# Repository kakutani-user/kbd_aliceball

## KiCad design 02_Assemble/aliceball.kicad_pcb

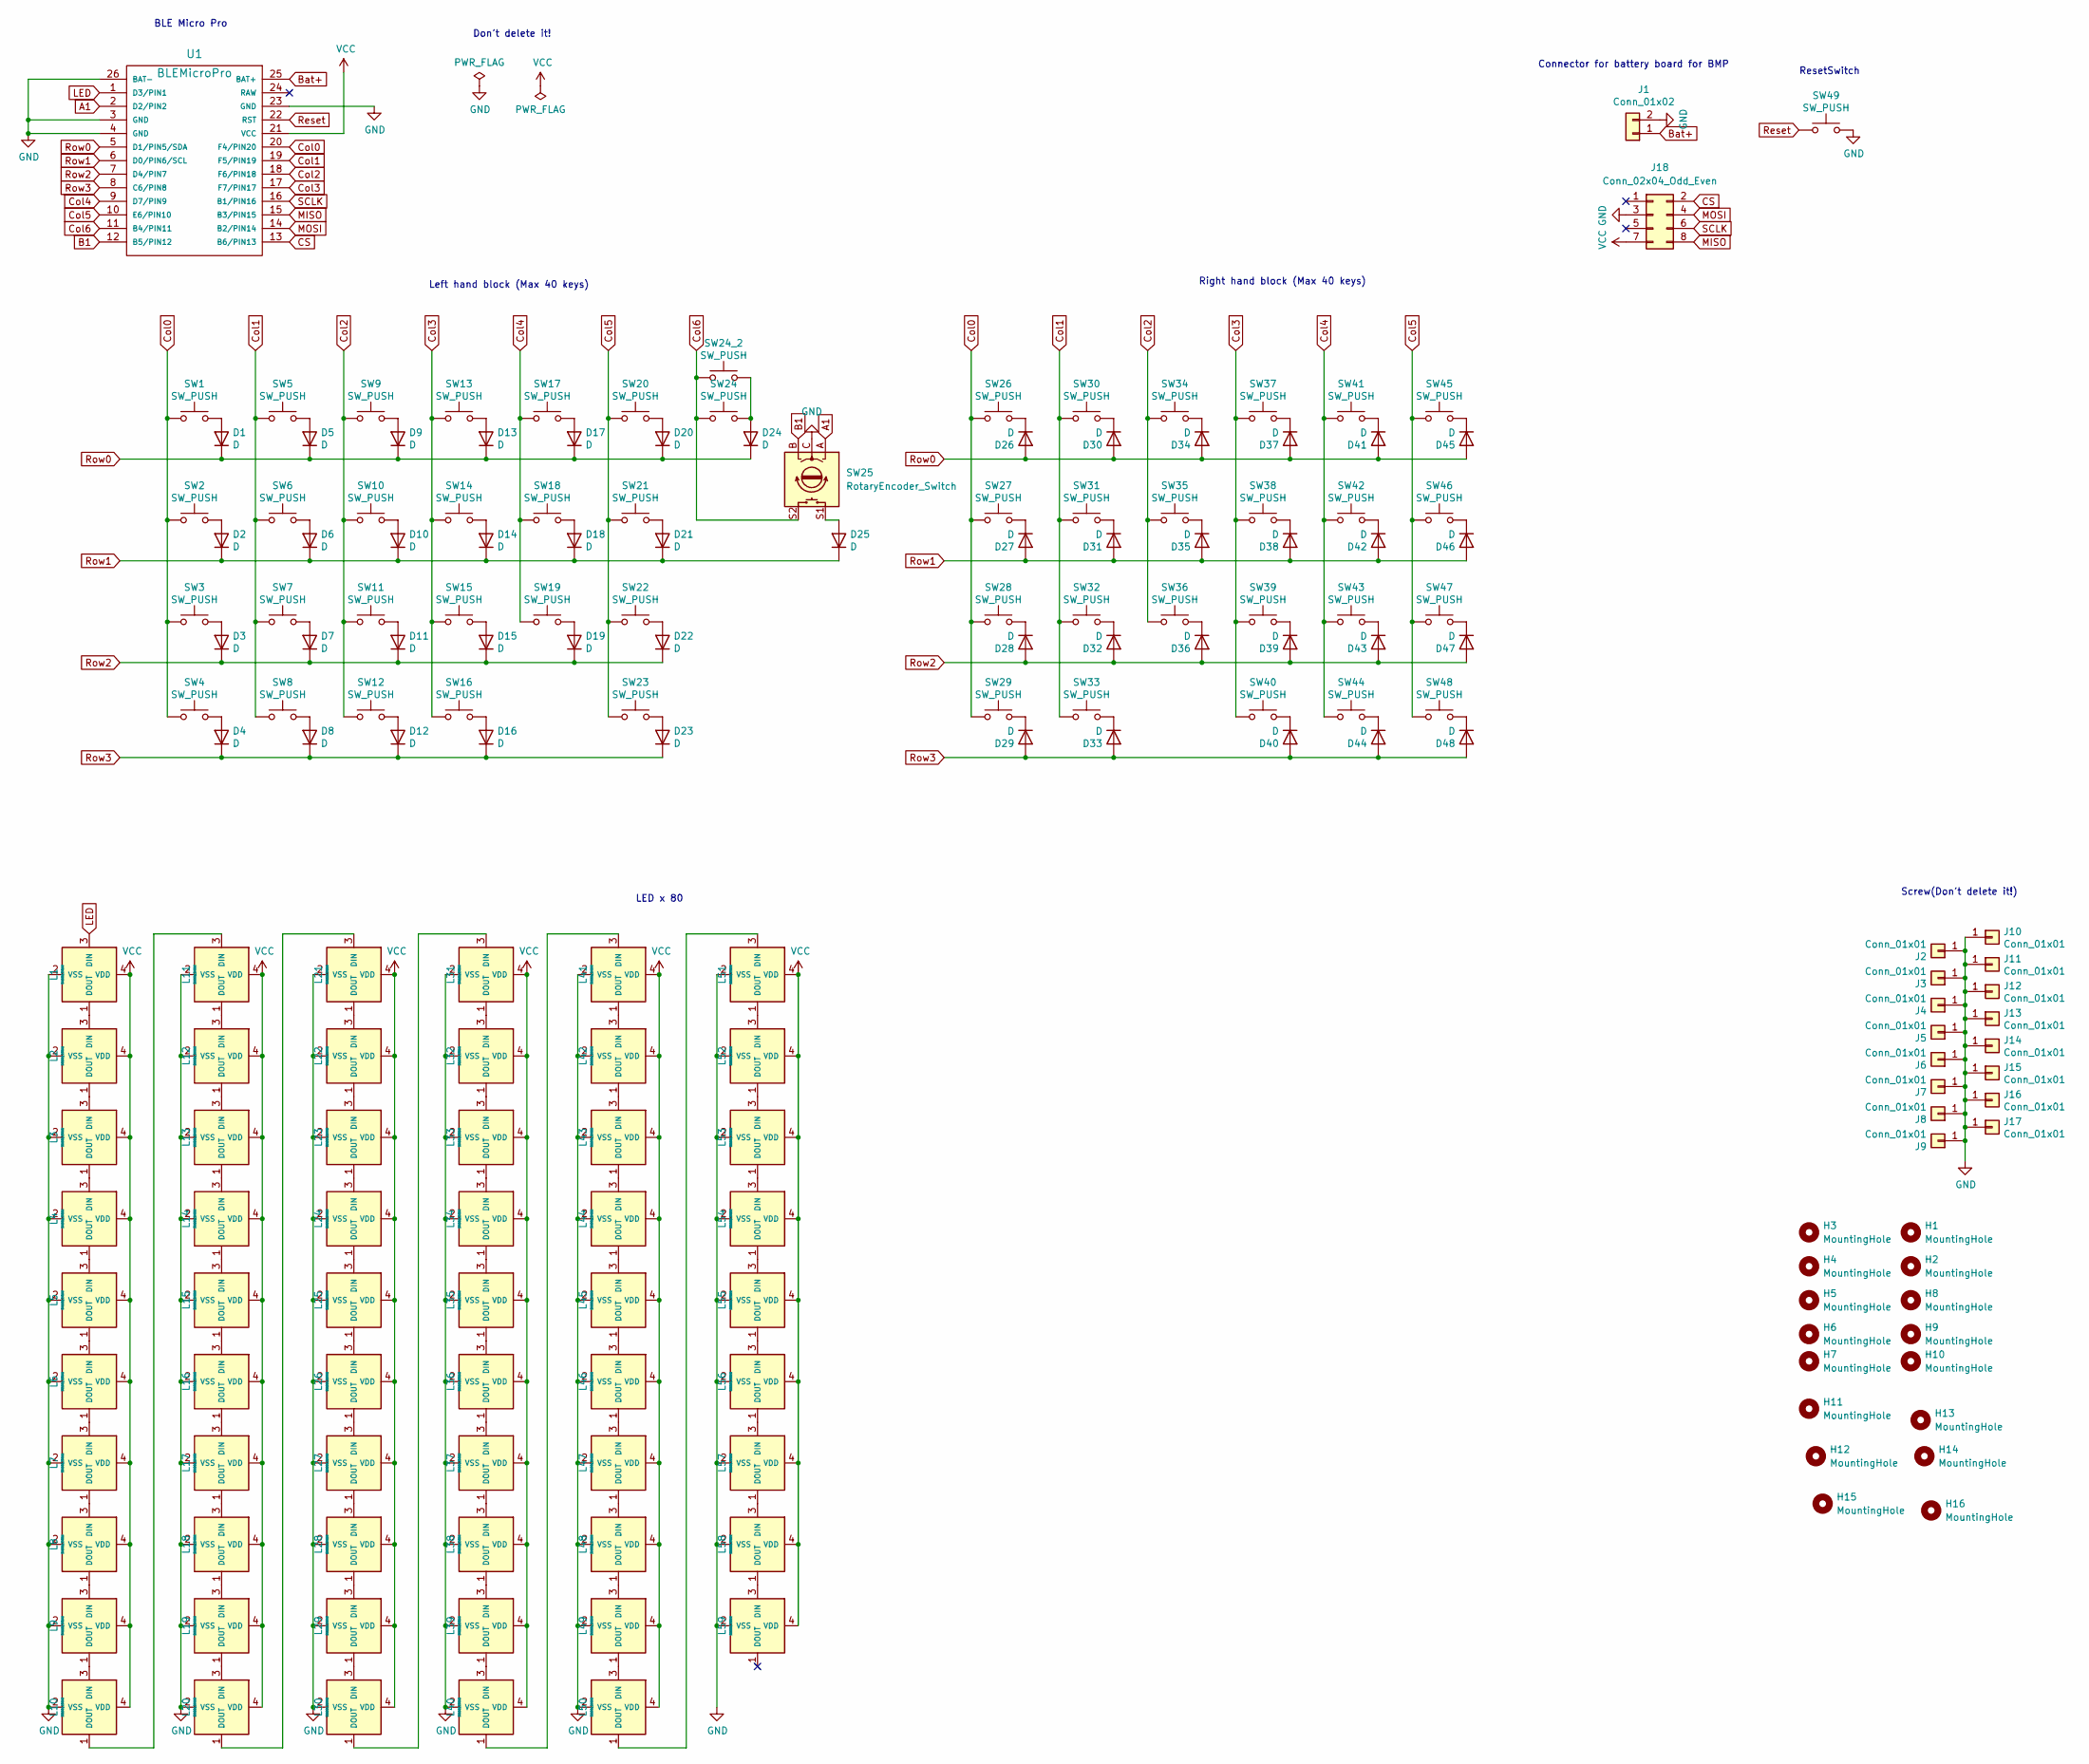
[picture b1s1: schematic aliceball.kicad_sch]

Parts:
D1, D2, D3, D4, D5, D6, D7, D8, D9, D10, D11, D12, D13, D14, D15, D16, D17, D18, D19, D20, D21, D22, D23, D24, D25, D26, D27, D28, D29, D30, D31, D32, D33, D34, D35, D36, D37, D38, D39, D40, D41, D42, D43, D44, D45, D46, D47, D48: D; Diode_TH_SMD
H1, H2, H3, H4, H5, H6, H7, H8, H9, H10, H11, H12, H13, H14, H15, H16: MountingHole; MountingHole_2.2mm_M2
J1: Conn_01x02; Battery_XH2.5_GL_PCB
J2, J3, J4, J5, J6, J7: Conn_01x01; m2_Screw_Hole_EdgeCuts
J8, J9, J10, J11, J12, J13, J14, J15, J16, J17: Conn_01x01; m2_Screw_Hole_Fab
J18: Conn_02x04_Odd_Even; ADNS-9800-module
L1, L2, L3, L4, L5, L6, L7, L8, L9, L10, L11, L12, L13, L14, L15, L16, L17, L18, L19, L20, L21, L22, L23, L24, L25, L26, L27, L28, L29, L30, L31, L32, L33, L34, L35, L36, L37, L38, L39, L40, L41, L42, L43, L44, L45, L46, L47, L48, L49, L50, L51, L52, L53, L54, L55, L56, L57, L58, L59: SK6812MINI; LED_SK6812MINI-E_BL
SW1, SW4, SW5, SW6, SW7, SW8, SW9, SW10, SW11, SW12, SW13, SW14, SW15, SW17, SW18, SW19, SW20, SW21, SW22, SW23, SW24, SW26, SW27, SW28, SW29, SW30, SW31, SW32, SW34, SW35, SW36, SW37, SW38, SW39, SW40, SW41, SW42, SW43, SW44, SW46, SW47, SW48: SW_PUSH; CherryMX_Hotswap_1.0u
SW2: SW_PUSH; CherryMX_Hotswap_1.25u
SW3: SW_PUSH; CherryMX_Hotswap_1.75u
SW16, SW33: SW_PUSH; CherryMX_Hotswap_2u
SW24_2, SW49: SW_PUSH; ResetSW
SW25: RotaryEncoder_Switch; RotaryEncoder_EC12E
SW45: SW_PUSH; CherryMX_Hotswap_1.5u
U1: BLEMicroPro; Micon_BMP_GL

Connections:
A1: SW25.A, U1.2 (D2/PIN2)
B1: SW25.B, U1.12 (B5/PIN12)
Bat+: J1.1, U1.25 (BAT+)
CS: J18.2, U1.13 (B6/PIN13)
Col0: SW1.1, SW2.1, SW3.1, SW4.1, SW26.1, SW27.1, SW28.1, SW29.1, U1.20 (F4/PIN20)
Col1: SW5.1, SW6.1, SW7.1, SW8.1, SW30.1, SW31.1, SW32.1, SW33.1, U1.19 (F5/PIN19)
Col2: SW9.1, SW10.1, SW11.1, SW12.1, SW34.1, SW35.1, SW36.1, U1.18 (F6/PIN18)
Col3: SW13.1, SW14.1, SW15.1, SW16.1, SW37.1, SW38.1, SW39.1, SW40.1, U1.17 (F7/PIN17)
Col4: SW17.1, SW18.1, SW19.1, SW41.1, SW42.1, SW43.1, SW44.1, U1.9 (D7/PIN9)
Col5: SW20.1, SW21.1, SW22.1, SW23.1, SW45.1, SW46.1, SW47.1, SW48.1, U1.10 (E6/PIN10)
Col6: SW24.1, SW24_2.1, SW25.S2, U1.11 (B4/PIN11)
GND: J1.2, J2.1, J3.1, J4.1, J5.1, J6.1, J7.1, J8.1, J9.1, J10.1, J11.1, J12.1, J13.1, J14.1, J15.1, J16.1, J17.1, J18.3, L1.2 (VSS), L2.2 (VSS), L3.2 (VSS), L4.2 (VSS), L5.2 (VSS), L6.2 (VSS), L7.2 (VSS), L8.2 (VSS), L9.2 (VSS), L10.2 (VSS), L11.2 (VSS), L12.2 (VSS), L13.2 (VSS), L14.2 (VSS), L15.2 (VSS), L16.2 (VSS), L17.2 (VSS), L18.2 (VSS), L19.2 (VSS), L20.2 (VSS), L21.2 (VSS), L22.2 (VSS), L23.2 (VSS), L24.2 (VSS), L25.2 (VSS), L26.2 (VSS), L27.2 (VSS), L28.2 (VSS), L29.2 (VSS), L30.2 (VSS), L31.2 (VSS), L32.2 (VSS), L33.2 (VSS), L34.2 (VSS), L35.2 (VSS), L36.2 (VSS), L37.2 (VSS), L38.2 (VSS), L39.2 (VSS), L40.2 (VSS), L41.2 (VSS), L42.2 (VSS), L43.2 (VSS), L44.2 (VSS), L45.2 (VSS), L46.2 (VSS), L47.2 (VSS), L48.2 (VSS), L49.2 (VSS), L50.2 (VSS), L51.2 (VSS), L52.2 (VSS), L53.2 (VSS), L54.2 (VSS), L55.2 (VSS), L56.2 (VSS), L57.2 (VSS), L58.2 (VSS), L59.2 (VSS), SW25.C, SW49.2, U1.3 (GND), U1.4 (GND), U1.23 (GND), U1.26 (BAT-)
LED: L1.3 (DIN), U1.1 (D3/PIN1)
MISO: J18.8, U1.15 (B3/PIN15)
MOSI: J18.4, U1.14 (B2/PIN14)
unnamed: D1.2 (A), SW1.2
unnamed: D2.2 (A), SW2.2
unnamed: D3.2 (A), SW3.2
unnamed: D4.2 (A), SW4.2
unnamed: D5.2 (A), SW5.2
unnamed: D6.2 (A), SW6.2
unnamed: D7.2 (A), SW7.2
unnamed: D8.2 (A), SW8.2
unnamed: D9.2 (A), SW9.2
unnamed: D10.2 (A), SW10.2
unnamed: D11.2 (A), SW11.2
unnamed: D12.2 (A), SW12.2
unnamed: D13.2 (A), SW13.2
unnamed: D14.2 (A), SW14.2
unnamed: D15.2 (A), SW15.2
unnamed: D16.2 (A), SW16.2
unnamed: D17.2 (A), SW17.2
unnamed: D18.2 (A), SW18.2
unnamed: D19.2 (A), SW19.2
unnamed: D20.2 (A), SW20.2
unnamed: D21.2 (A), SW21.2
unnamed: D22.2 (A), SW22.2
unnamed: D23.2 (A), SW23.2
unnamed: D24.2 (A), SW24.2, SW24_2.2
unnamed: D25.2 (A), SW25.S1
unnamed: D26.1 (K), SW26.2
unnamed: D27.1 (K), SW27.2
unnamed: D28.1 (K), SW28.2
unnamed: D29.1 (K), SW29.2
unnamed: D30.1 (K), SW30.2
unnamed: D31.1 (K), SW31.2
unnamed: D32.1 (K), SW32.2
unnamed: D33.1 (K), SW33.2
unnamed: D34.1 (K), SW34.2
unnamed: D35.1 (K), SW35.2
unnamed: D36.1 (K), SW36.2
unnamed: D37.1 (K), SW37.2
unnamed: D38.1 (K), SW38.2
unnamed: D39.1 (K), SW39.2
unnamed: D40.1 (K), SW40.2
unnamed: D41.1 (K), SW41.2
unnamed: D42.1 (K), SW42.2
unnamed: D43.1 (K), SW43.2
unnamed: D44.1 (K), SW44.2
unnamed: D45.1 (K), SW45.2
unnamed: D46.1 (K), SW46.2
unnamed: D47.1 (K), SW47.2
unnamed: D48.1 (K), SW48.2
unnamed: L1.1 (DOUT), L2.3 (DIN)
unnamed: L2.1 (DOUT), L3.3 (DIN)
unnamed: L3.1 (DOUT), L4.3 (DIN)
unnamed: L4.1 (DOUT), L5.3 (DIN)
unnamed: L5.1 (DOUT), L6.3 (DIN)
unnamed: L6.1 (DOUT), L7.3 (DIN)
unnamed: L7.1 (DOUT), L8.3 (DIN)
unnamed: L8.1 (DOUT), L9.3 (DIN)
unnamed: L10.1 (DOUT), L11.3 (DIN)
unnamed: L9.1 (DOUT), L10.3 (DIN)
unnamed: L11.1 (DOUT), L12.3 (DIN)
unnamed: L12.1 (DOUT), L13.3 (DIN)
unnamed: L13.1 (DOUT), L14.3 (DIN)
unnamed: L14.1 (DOUT), L15.3 (DIN)
unnamed: L15.1 (DOUT), L16.3 (DIN)
unnamed: L16.1 (DOUT), L17.3 (DIN)
unnamed: L17.1 (DOUT), L18.3 (DIN)
unnamed: L18.1 (DOUT), L19.3 (DIN)
unnamed: L19.1 (DOUT), L20.3 (DIN)
unnamed: L20.1 (DOUT), L21.3 (DIN)
unnamed: L21.1 (DOUT), L22.3 (DIN)
unnamed: L22.1 (DOUT), L23.3 (DIN)
unnamed: L23.1 (DOUT), L24.3 (DIN)
unnamed: L24.1 (DOUT), L25.3 (DIN)
unnamed: L25.1 (DOUT), L26.3 (DIN)
unnamed: L26.1 (DOUT), L27.3 (DIN)
unnamed: L27.1 (DOUT), L28.3 (DIN)
unnamed: L28.1 (DOUT), L29.3 (DIN)
unnamed: L29.1 (DOUT), L30.3 (DIN)
unnamed: L30.1 (DOUT), L31.3 (DIN)
unnamed: L31.1 (DOUT), L32.3 (DIN)
unnamed: L32.1 (DOUT), L33.3 (DIN)
unnamed: L33.1 (DOUT), L34.3 (DIN)
unnamed: L34.1 (DOUT), L35.3 (DIN)
unnamed: L35.1 (DOUT), L36.3 (DIN)
unnamed: L36.1 (DOUT), L37.3 (DIN)
unnamed: L37.1 (DOUT), L38.3 (DIN)
unnamed: L38.1 (DOUT), L39.3 (DIN)
unnamed: L39.1 (DOUT), L40.3 (DIN)
unnamed: L40.1 (DOUT), L41.3 (DIN)
unnamed: L41.1 (DOUT), L42.3 (DIN)
unnamed: L42.1 (DOUT), L43.3 (DIN)
unnamed: L43.1 (DOUT), L44.3 (DIN)
unnamed: L44.1 (DOUT), L45.3 (DIN)
unnamed: L45.1 (DOUT), L46.3 (DIN)
unnamed: L46.1 (DOUT), L47.3 (DIN)
unnamed: L47.1 (DOUT), L48.3 (DIN)
unnamed: L48.1 (DOUT), L49.3 (DIN)
unnamed: L49.1 (DOUT), L50.3 (DIN)
unnamed: L50.1 (DOUT), L51.3 (DIN)
unnamed: L51.1 (DOUT), L52.3 (DIN)
unnamed: L52.1 (DOUT), L53.3 (DIN)
unnamed: L53.1 (DOUT), L54.3 (DIN)
unnamed: L54.1 (DOUT), L55.3 (DIN)
unnamed: L55.1 (DOUT), L56.3 (DIN)
unnamed: L56.1 (DOUT), L57.3 (DIN)
unnamed: L57.1 (DOUT), L58.3 (DIN)
unnamed: L58.1 (DOUT), L59.3 (DIN)
Reset: SW49.1, U1.22 (RST)
Row0: D1.1 (K), D5.1 (K), D9.1 (K), D13.1 (K), D17.1 (K), D20.1 (K), D24.1 (K), D26.2 (A), D30.2 (A), D34.2 (A), D37.2 (A), D41.2 (A), D45.2 (A), U1.5 (D1/PIN5/SDA)
Row1: D2.1 (K), D6.1 (K), D10.1 (K), D14.1 (K), D18.1 (K), D21.1 (K), D25.1 (K), D27.2 (A), D31.2 (A), D35.2 (A), D38.2 (A), D42.2 (A), D46.2 (A), U1.6 (D0/PIN6/SCL)
Row2: D3.1 (K), D7.1 (K), D11.1 (K), D15.1 (K), D19.1 (K), D22.1 (K), D28.2 (A), D32.2 (A), D36.2 (A), D39.2 (A), D43.2 (A), D47.2 (A), U1.7 (D4/PIN7)
Row3: D4.1 (K), D8.1 (K), D12.1 (K), D16.1 (K), D23.1 (K), D29.2 (A), D33.2 (A), D40.2 (A), D44.2 (A), D48.2 (A), U1.8 (C6/PIN8)
SCLK: J18.6, U1.16 (B1/PIN16)
VCC: J18.7, L1.4 (VDD), L2.4 (VDD), L3.4 (VDD), L4.4 (VDD), L5.4 (VDD), L6.4 (VDD), L7.4 (VDD), L8.4 (VDD), L9.4 (VDD), L10.4 (VDD), L11.4 (VDD), L12.4 (VDD), L13.4 (VDD), L14.4 (VDD), L15.4 (VDD), L16.4 (VDD), L17.4 (VDD), L18.4 (VDD), L19.4 (VDD), L20.4 (VDD), L21.4 (VDD), L22.4 (VDD), L23.4 (VDD), L24.4 (VDD), L25.4 (VDD), L26.4 (VDD), L27.4 (VDD), L28.4 (VDD), L29.4 (VDD), L30.4 (VDD), L31.4 (VDD), L32.4 (VDD), L33.4 (VDD), L34.4 (VDD), L35.4 (VDD), L36.4 (VDD), L37.4 (VDD), L38.4 (VDD), L39.4 (VDD), L40.4 (VDD), L41.4 (VDD), L42.4 (VDD), L43.4 (VDD), L44.4 (VDD), L45.4 (VDD), L46.4 (VDD), L47.4 (VDD), L48.4 (VDD), L49.4 (VDD), L50.4 (VDD), L51.4 (VDD), L52.4 (VDD), L53.4 (VDD), L54.4 (VDD), L55.4 (VDD), L56.4 (VDD), L57.4 (VDD), L58.4 (VDD), L59.4 (VDD), U1.21 (VCC)

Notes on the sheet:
BLE Micro Pro
Right hand block (Max 40 keys)
Don't delete it!
Screw(Don't delete it!)
LED x 80
Left hand block (Max 40 keys)
Connector for battery board for BMP
ResetSwitch

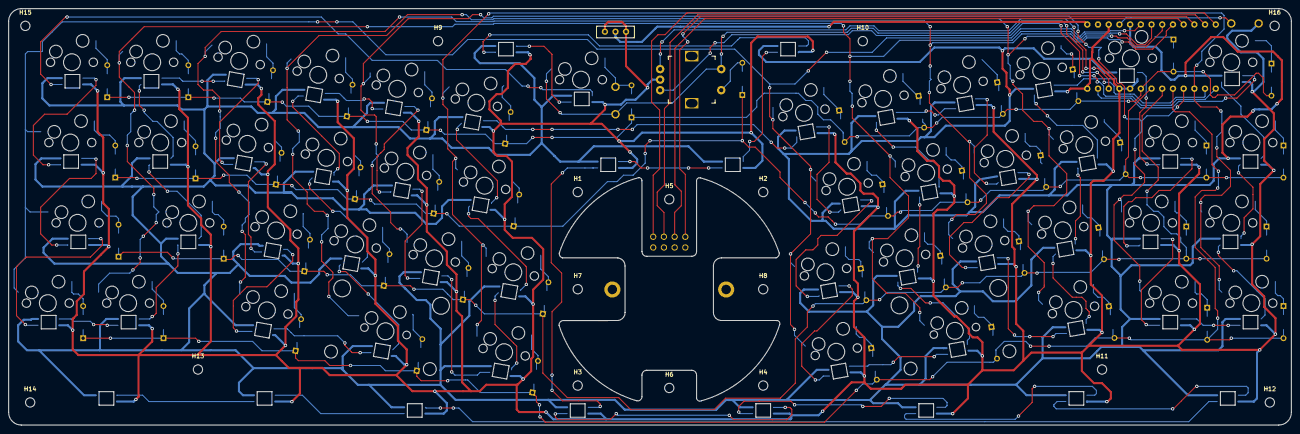
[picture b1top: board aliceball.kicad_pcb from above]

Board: 2 copper layers, 304.4 x 98.8 mm, 176 parts (1 on the bottom side), 128 nets.

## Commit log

2021-12-31 build aliceball rev0.1
2021-12-31 delte DS_Store
2021-12-31 adjust silkscreen
2021-12-31 modify route
2022-01-02 add bmp version
2022-02-28 rev 0.2
